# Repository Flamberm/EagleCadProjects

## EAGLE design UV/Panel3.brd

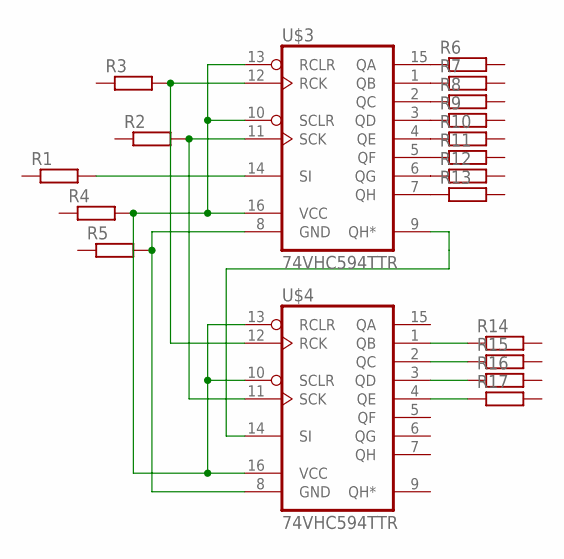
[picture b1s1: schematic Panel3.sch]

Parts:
R1, R2, R3, R4, R5, R6, R7, R8, R9, R10, R11, R12, R13, R14, R15, R16, R17: R_0805; R0805
U$3, U$4: 74VHC594TTR; TSSOP16

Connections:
unnamed: U$3.9 (QH*), U$4.14 (SI)
unnamed: R4.2, U$3.10 (SCLR), U$3.13 (RCLR), U$3.16 (VCC), U$4.10 (SCLR), U$4.13 (RCLR), U$4.16 (VCC)
unnamed: R6.1, U$3.15 (QA)
unnamed: R2.2, U$3.11 (SCK), U$4.11 (SCK)
unnamed: R7.1, U$3.1 (QB)
unnamed: R3.2, U$3.12 (RCK), U$4.12 (RCK)
unnamed: R1.2, U$3.14 (SI)
unnamed: R8.1, U$3.2 (QC)
unnamed: R5.2, U$3.8 (GND), U$4.8 (GND)
unnamed: R9.1, U$3.3 (QD)
unnamed: R10.1, U$3.4 (QE)
unnamed: R11.1, U$3.5 (QF)
unnamed: R12.1, U$3.6 (QG)
unnamed: R13.1, U$3.7 (QH)
unnamed: R14.1, U$4.1 (QB)
unnamed: R15.1, U$4.2 (QC)
unnamed: R16.1, U$4.3 (QD)
unnamed: R17.1, U$4.4 (QE)

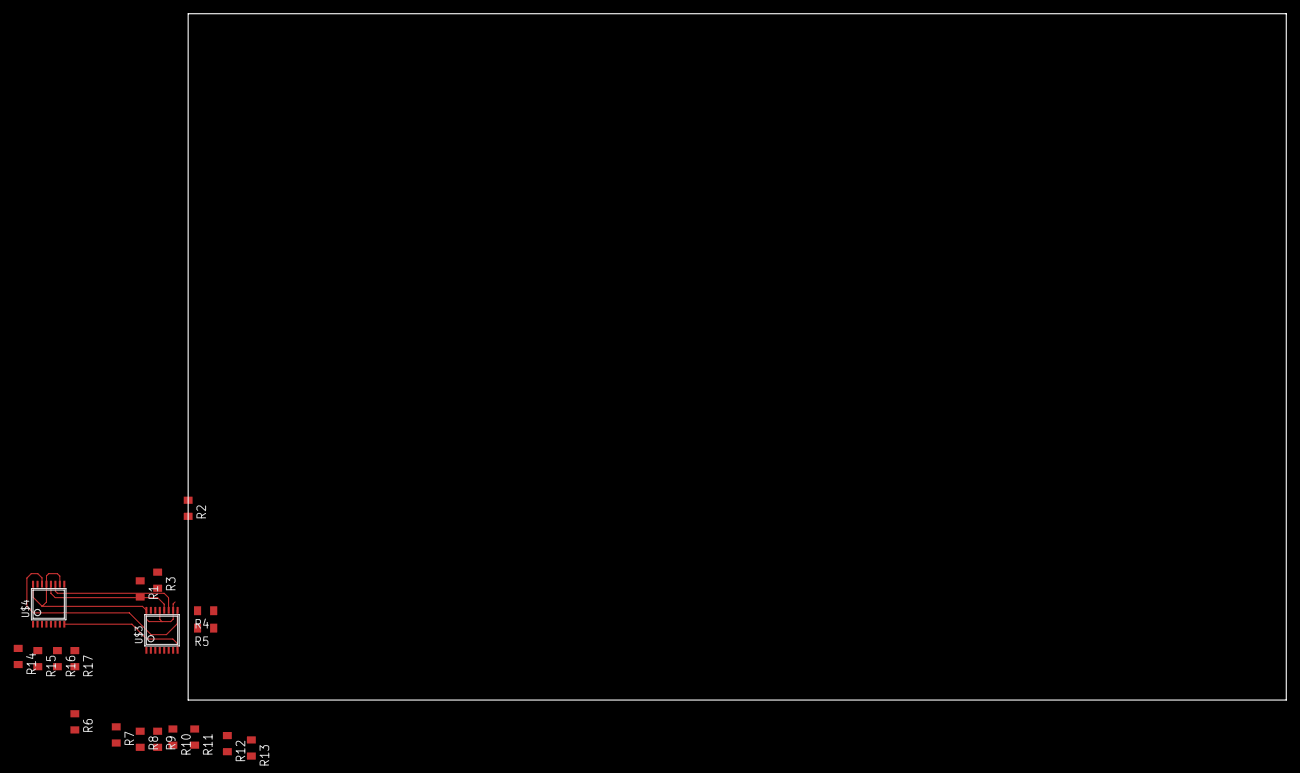
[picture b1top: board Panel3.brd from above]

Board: 2 copper layers, 160.0 x 100.0 mm, 19 parts (0 on the bottom side), 18 nets.

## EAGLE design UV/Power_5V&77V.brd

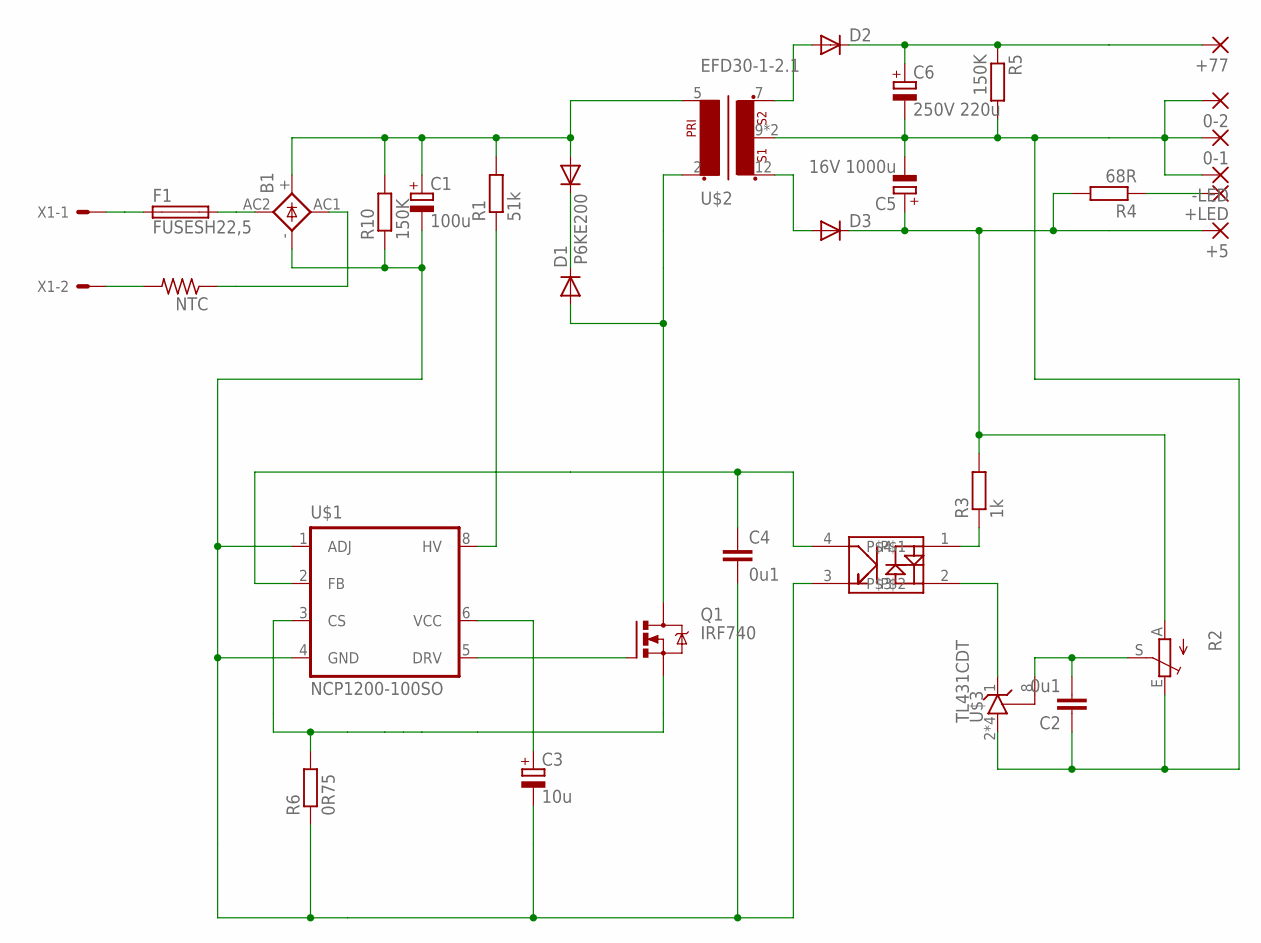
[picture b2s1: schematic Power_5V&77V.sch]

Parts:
0-1: 2,54/0,8
0-2: 3,17/1,1
+5: 2,54/0,8
+77: 3,17/1,1
+LED: 2,54/0,8
-LED: 2,54/0,8
B1: KBL
C1: 100u; EB25D
C2, C4: 0u1; C1206
C3: 10u; E2,5-5
C5: 16V 1000u; E3,5-8
C6: 250V 220u; EB22,5D
D1: DIODE-DO-214AC; DO-214AC
D2: DIODE-TO220V; TO220ACS
D3: DIODE-SMB; SMB
F1: FUSESH22,5; SH22,5
NTC: R-US_0207/10; 0207/10
P6KE200: DIODE-SMB; SMB
Q1: IRF740; TO220BV
R1: 51k; 0922/22
R2: TRIM_EU-S75H; S75H
R3: 1k; R1206
R4: 68R; R1206
R5: 150K; R1206
R6: 0R75; 0411/15
R10: 150K; 0207/10
U$1: NCP1200-100SO; SOP8
U$2: EFD30-1-2.1; EFD30_1-2.1
U$3: TL431CDT; SO8
U$5: EL3H4(TA)-VG; SSOP4
X1: KK-156-2

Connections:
unnamed: NTC.2, X1.2
unnamed: F1.1, X1.1
unnamed: B1.AC1 (AC2), NTC.1
unnamed: B1.AC2 (AC1), F1.2
unnamed: C4.1, U$1.2 (FB), U$5.4
unnamed: B1.+, C1.+, P6KE200.A, R1.2, R10.2, U$2.5 (P1-2)
unnamed: D1.C, P6KE200.C
unnamed: D1.A, Q1.D, U$2.2 (P1-1)
unnamed: C2.2, R2.S, U$3.8 (R)
unnamed: R1.1, U$1.8 (HV)
unnamed: Q1.G, U$1.5 (DRV)
unnamed: Q1.S, R6.2, U$1.3 (CS)
unnamed: R3.1, U$5.1
unnamed: C3.+, U$1.6 (VCC)
unnamed: U$3.1 (C), U$5.2
unnamed: B1.-, C1.-, C3.-, C4.2, R6.1, R10.1, U$1.1 (ADJ), U$1.4 (GND), U$5.3
unnamed: D2.A, U$2.7 (S2)
unnamed: 0-1.1, 0-2.1, -LED.1, C2.1, C5.-, C6.-, R2.E, R5.2, U$2.9 (S0), U$2.10 (S0), U$3.2 (A), U$3.3 (A), U$3.6 (A), U$3.7 (A)
unnamed: +5.1, C5.+, D3.C, R2.A, R3.2, R4.2
unnamed: +77.1, C6.+, D2.C, R5.1
unnamed: D3.A, U$2.12 (S1)
unnamed: +LED.1, R4.1

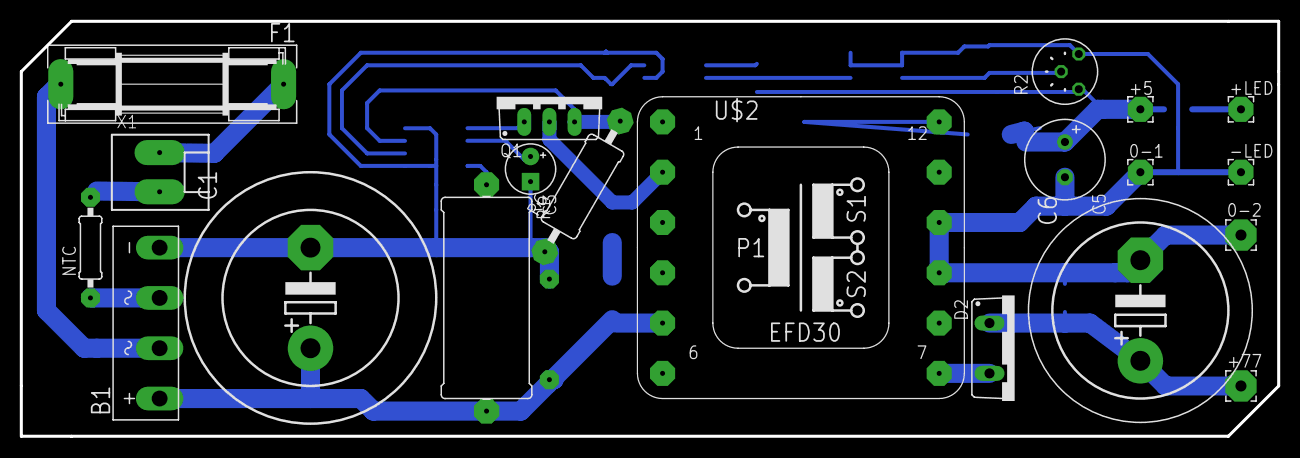
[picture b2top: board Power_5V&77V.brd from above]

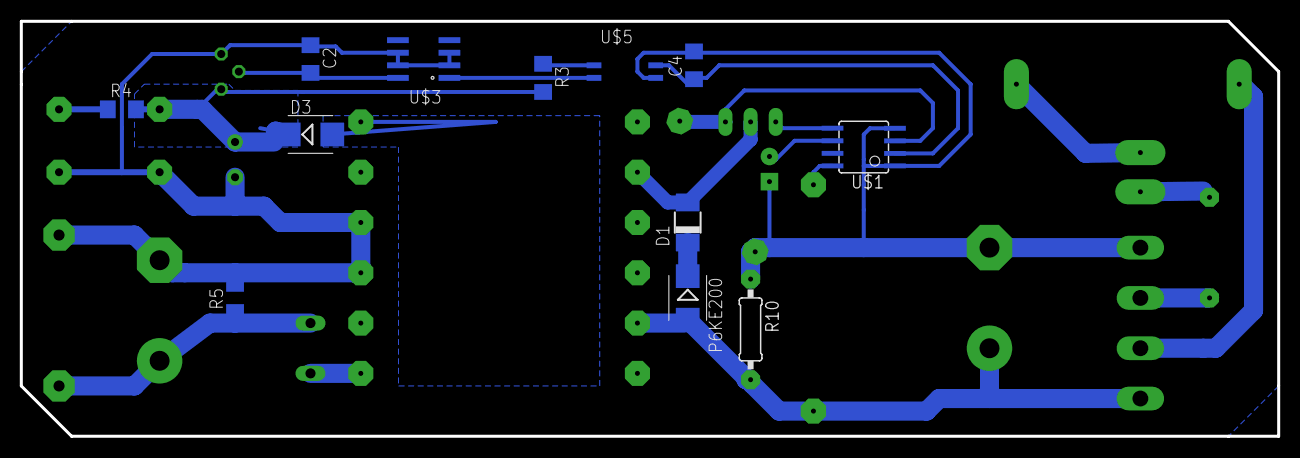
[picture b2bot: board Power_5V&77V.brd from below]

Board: 2 copper layers, 127.0 x 41.9 mm, 32 parts (12 on the bottom side), 22 nets.

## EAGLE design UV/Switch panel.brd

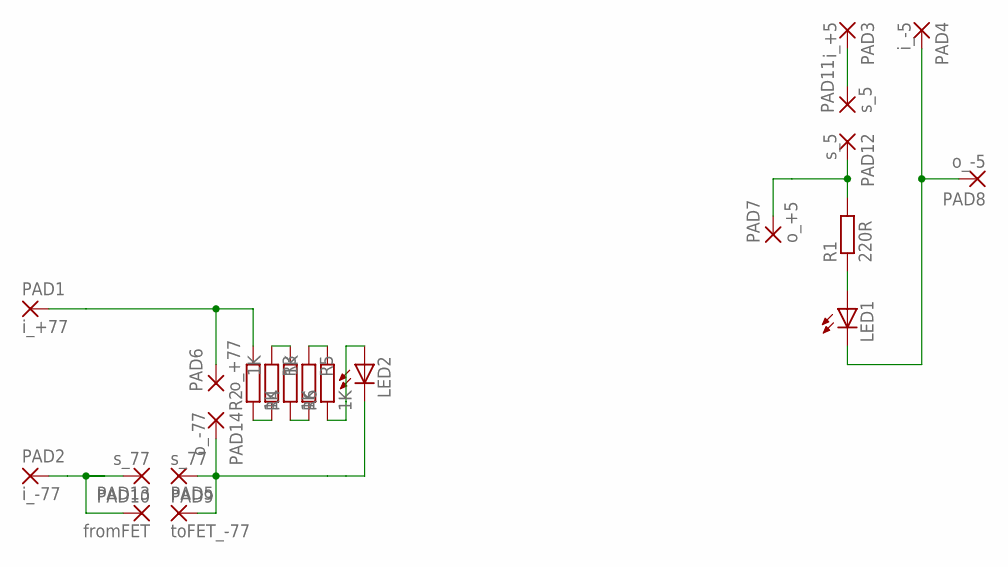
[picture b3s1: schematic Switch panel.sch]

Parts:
LED1, LED2: LED3MM
PAD1: i_+77; SMD2,54-5,08
PAD2: i_-77; SMD2,54-5,08
PAD3: i_+5; SMD2,54-5,08
PAD4: i_-5; SMD2,54-5,08
PAD5: toFET_-77; SMD2,54-5,08
PAD6: o_+77; SMD2,54-5,08
PAD7: o_+5; SMD2,54-5,08
PAD8: o_-5; SMD2,54-5,08
PAD9, PAD10: s_77; SMD2,54-5,08
PAD11, PAD12: s_5; SMD2,54-5,08
PAD13: fromFET; SMD2,54-5,08
PAD14: o_-77; SMD2,54-5,08
R1: 220R; R1206
R2, R3, R4, R5, R6: 1K; R1206

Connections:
unnamed: PAD7.1, PAD12.1, R1.2
unnamed: LED1.A, R1.1
unnamed: LED1.K (C), PAD4.1, PAD8.1
unnamed: PAD3.1, PAD11.1
unnamed: R2.1, R3.2
unnamed: R3.1, R4.2
unnamed: R4.1, R5.2
unnamed: R5.1, R6.2
unnamed: PAD1.1, PAD6.1, R2.2
unnamed: LED2.A, R6.1
unnamed: LED2.K (C), PAD5.1, PAD9.1, PAD14.1
unnamed: PAD2.1, PAD10.1, PAD13.1

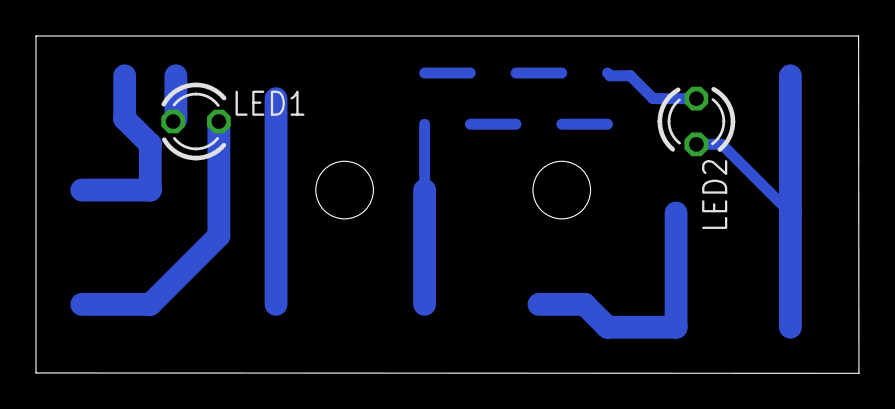
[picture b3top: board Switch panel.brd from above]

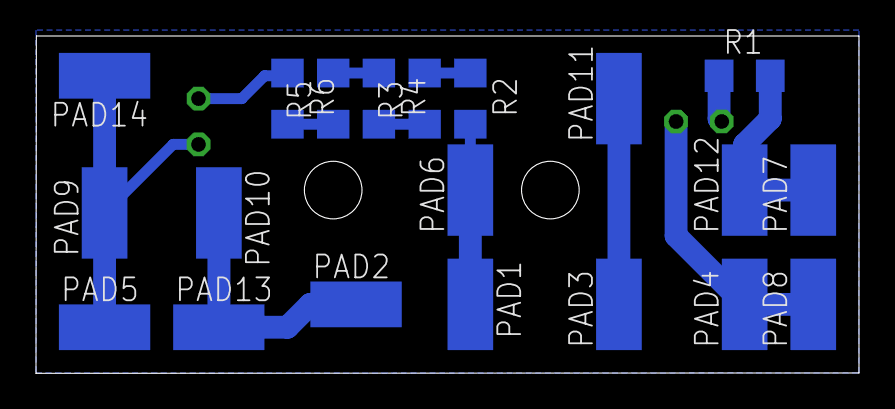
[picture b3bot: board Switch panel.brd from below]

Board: 2 copper layers, 45.7 x 18.7 mm, 22 parts (20 on the bottom side), 12 nets.
